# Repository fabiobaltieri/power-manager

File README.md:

USB Power Manager
=================

http://fabiobaltieri.com/2013/03/22/power-manager/

This project is an USB power controller, and allows to control the power lines
of two USB ports and a generic supply line.

Main features:
- Two controllable USB ports (5V)
- One controllable generic supply line, up to 26V
- Overcurrent protection for USB ports
- Voltage and current measurement on both USB and power ports, before and after
  the switch
- Two additional independent relay lines (for switch simulation)
- Programmable delayed switching sequence for all ports

License
-------

This program is free software: you can redistribute it and/or modify
it under the terms of the GNU General Public License as published by
the Free Software Foundation, either version 2 of the License, or
(at your option) any later version.

Contents
--------

    COPYING      text version of the GPL
    README       this file
    bootloader/  source directory for bootloader
    bootloader-util/ source directory for bootloader utility (bootloadHID)
    commandline/ source directory for the "pm" utility
    firmware/    source directory for main firmware
    hardware/    source directory for the hardware design

Firmware and Bootloader
-----------------------

Building requires an avr-gcc toolchain, in the firmware/ or bootloader/
directory, to build run:

    make

Flashing the firmware on the device requires avrdude and a compatible hardware
programmer. Default configuration is stored at the beginning of the Makefile.
To program with the default configuration, run:

    make flash

Fuses can be configured running:

    make fuses

To program the main firmware from the bootloader, use the command:

    make boot

Hardware
--------

All hardware files (schematic, layout and libraries) are in CadSoft Eagle
format.

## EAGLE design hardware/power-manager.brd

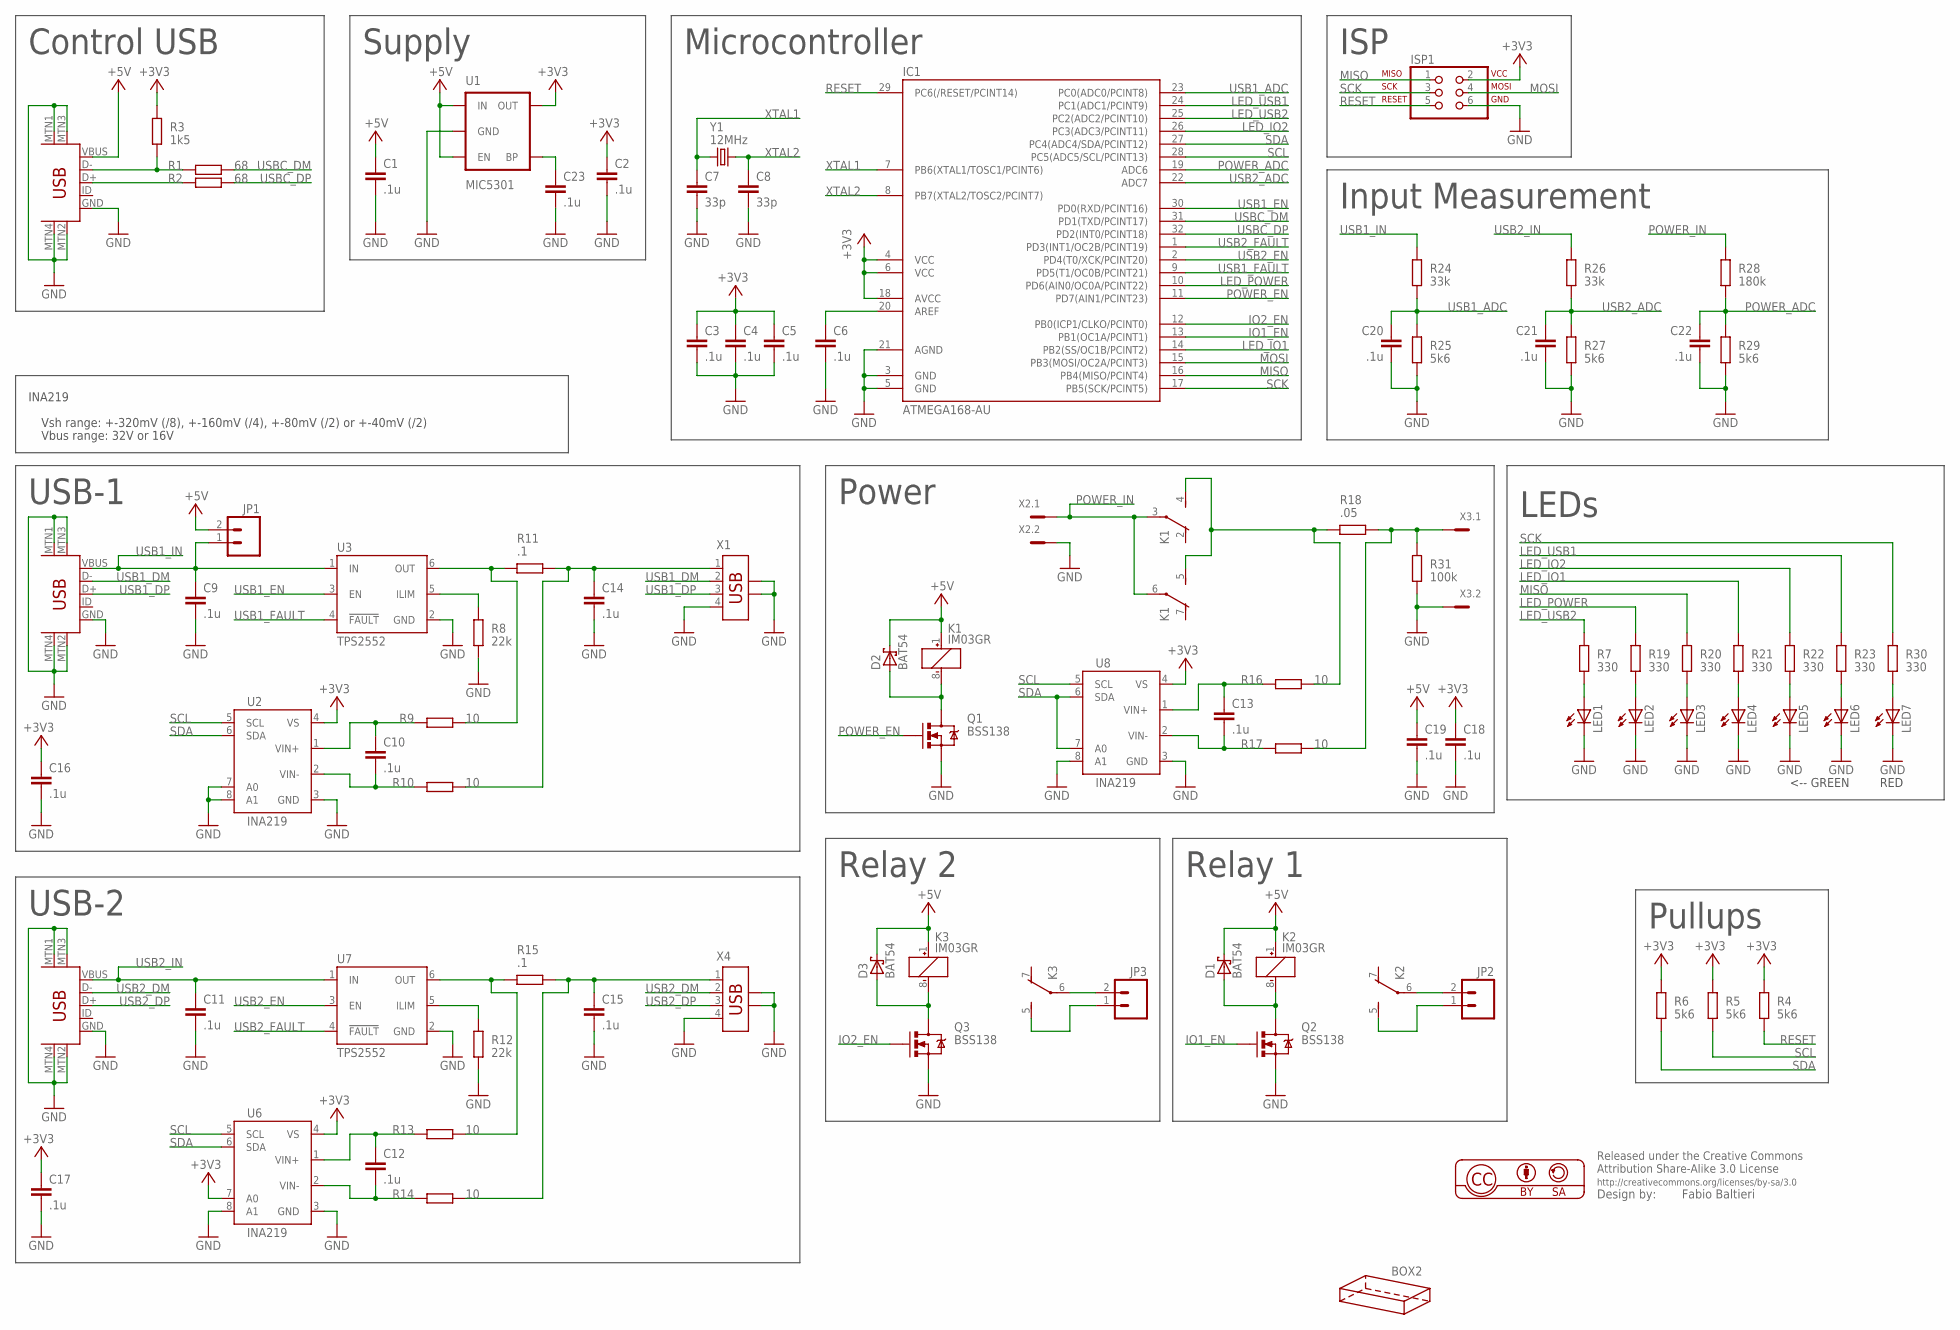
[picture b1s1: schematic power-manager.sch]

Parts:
BOX2: HAMMOND-BOX-K; 1551K
C1, C2, C3, C4, C5, C6, C9, C10, C11, C12, C13, C14, C15, C16, C17, C18, C19, C20, C21, C22, C23: .1u; C0805
C7, C8: 33p; C0805
D1, D2, D3: BAT54; SOT23
IC1: ATMEGA168-AU; TQFP32-08
ISP1: ISP-AVR910PTH; 2X03
JP1, JP2, JP3: M02PTH; 1X02
K1, K2, K3: IM03GR; G6J-2FL-Y
LED1, LED2, LED3, LED4, LED5, LED6, LED7: LEDSML0805; SML0805
Q1, Q2, Q3: BSS138; SOT23-3
R1, R2: 68; R0603
R3: 1k5; R0603
R4, R5, R6, R25, R27, R29: 5k6; R0603
R7, R19, R20, R21, R22, R23, R30: 330; R0603
R8, R12: 22k; R0603
R9, R10, R13, R14, R16, R17: 10; R0603
R11, R15: .1; R0805
R18: .05; R0805
R24, R26: 33k; R0603
R28: 180k; R0603
R31: 100k; R0603
U1: MIC5301; SOT23-5
U2, U6, U8: INA219; SOT23-8L
U3, U7: TPS2552; SOT23-6L
U$1, U$2, U$3: USB-MINIB-5PIN; USB-MINIB
X1, X4: USB-787616; USB
X2, X3: MC2
Y1: 12MHz; CRYSTAL-SMD-5X3

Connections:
+3V3: C2.1, C3.1, C4.1, C5.1, C16.1, C17.1, C18.1, IC1.4 (VCC), IC1.6 (VCC), IC1.18 (AVCC), ISP1.2, R3.1, R4.1, R5.1, R6.1, U1.5 (OUT), U2.4 (VS), U6.4 (VS), U6.7 (A0), U8.4 (VS)
+5V: C1.1, C19.1, D1.3 (C), D2.3 (C), D3.3 (C), JP1.2, K1.1 (+), K2.1 (+), K3.1 (+), U1.1 (IN), U1.3 (EN), U$1.VBUS
GND: C1.2, C2.2, C3.2, C4.2, C5.2, C6.2, C7.2, C8.2, C9.2, C11.2, C14.2, C15.2, C16.2, C17.2, C18.2, C19.2, C20.2, C21.2, C22.2, C23.2, IC1.3 (GND), IC1.5 (GND), IC1.21 (AGND), ISP1.6, LED1.C, LED2.C, LED3.C, LED4.C, LED5.C, LED6.C, LED7.C, Q1.2 (S), Q2.2 (S), Q3.2 (S), R8.2, R12.2, R25.2, R27.2, R29.2, R31.2, U1.2 (GND), U2.3 (GND), U2.7 (A0), U2.8 (A1), U3.2 (GND), U6.3 (GND), U6.8 (A1), U7.2 (GND), U8.3 (GND), U8.8 (A1), U$1.GND, U$1.MTN1 (MTN2), U$1.MTN2 (MTN3), U$1.MTN3 (MTN1), U$1.MTN4, U$2.GND, U$2.MTN1 (MTN2), U$2.MTN2 (MTN3), U$2.MTN3 (MTN1), U$2.MTN4, U$3.GND, U$3.MTN1 (MTN2), U$3.MTN2 (MTN3), U$3.MTN3 (MTN1), U$3.MTN4, X1.4, X1.SHLD1, X1.SHLD2, X2.2, X3.2, X4.4, X4.SHLD1, X4.SHLD2
IO1_EN: IC1.13 (PB1(OC1A/PCINT1)), Q2.1 (G)
IO2_EN: IC1.12 (PB0(ICP1/CLKO/PCINT0)), Q3.1 (G)
LED_IO1: IC1.14 (PB2(SS/OC1B/PCINT2)), R21.1
LED_IO2: IC1.26 (PC3(ADC3/PCINT11)), R22.1
LED_POWER: IC1.10 (PD6(AIN0/OC0A/PCINT22)), R19.1
LED_USB1: IC1.24 (PC1(ADC1/PCINT9)), R23.1
LED_USB2: IC1.25 (PC2(ADC2/PCINT10)), R7.1
MISO: IC1.16 (PB4(MISO/PCINT4)), ISP1.1, R20.1
MOSI: IC1.15 (PB3(MOSI/OC2A/PCINT3)), ISP1.4
unnamed: R1.1, R3.2, U$1.D-
unnamed: C6.1, IC1.20 (AREF)
unnamed: R2.1, U$1.D+
unnamed: R8.1, U3.5 (ILIM)
unnamed: C23.1, U1.4 (BP)
unnamed: C10.2, R10.1, U2.2 (VIN-)
unnamed: C10.1, R9.1, U2.1 (VIN+)
unnamed: R9.2, R11.1, U3.6 (OUT)
unnamed: C14.1, R10.2, R11.2, X1.1
unnamed: LED7.A, R30.2
unnamed: R12.1, U7.5 (ILIM)
unnamed: C12.2, R14.1, U6.2 (VIN-)
unnamed: C12.1, R13.1, U6.1 (VIN+)
unnamed: R13.2, R15.1, U7.6 (OUT)
unnamed: C15.1, R14.2, R15.2, X4.1
unnamed: C13.2, R17.1, U8.2 (VIN-)
unnamed: C13.1, R16.1, U8.1 (VIN+)
unnamed: K1.4 (S), K1.5 (S), R16.2, R18.1
unnamed: R17.2, R18.2, R31.1, X3.1
unnamed: D2.1 (A), K1.8 (-), Q1.3 (D)
unnamed: D1.1 (A), K2.8 (-), Q2.3 (D)
unnamed: JP2.2, K2.6
unnamed: JP2.1, K2.5 (S)
unnamed: D3.1 (A), K3.8 (-), Q3.3 (D)
unnamed: JP3.2, K3.6
unnamed: JP3.1, K3.5 (S)
unnamed: LED1.A, R7.2
unnamed: LED2.A, R19.2
unnamed: LED3.A, R20.2
unnamed: LED4.A, R21.2
unnamed: LED5.A, R22.2
unnamed: LED6.A, R23.2
POWER_ADC: C22.1, IC1.19 (ADC6), R28.2, R29.1
POWER_EN: IC1.11 (PD7(AIN1/PCINT23)), Q1.1 (G)
POWER_IN: K1.3, K1.6, R28.1, X2.1
RESET: IC1.29 (PC6(/RESET/PCINT14)), ISP1.5, R4.2
SCK: IC1.17 (PB5(SCK/PCINT5)), ISP1.3, R30.1
SCL: IC1.28 (PC5(ADC5/SCL/PCINT13)), R5.2, U2.5 (SCL), U6.5 (SCL), U8.5 (SCL)
SDA: IC1.27 (PC4(ADC4/SDA/PCINT12)), R6.2, U2.6 (SDA), U6.6 (SDA), U8.6 (SDA), U8.7 (A0)
USB1_ADC: C20.1, IC1.23 (PC0(ADC0/PCINT8)), R24.2, R25.1
USB1_DM: U$2.D-, X1.2
USB1_DP: U$2.D+, X1.3
USB1_EN: IC1.30 (PD0(RXD/PCINT16)), U3.3 (EN)
USB1_FAULT: IC1.9 (PD5(T1/OC0B/PCINT21)), U3.4 (!FAULT)
USB1_IN: C9.1, JP1.1, R24.1, U3.1 (IN), U$2.VBUS
USB2_ADC: C21.1, IC1.22 (ADC7), R26.2, R27.1
USB2_DM: U$3.D-, X4.2
USB2_DP: U$3.D+, X4.3
USB2_EN: IC1.2 (PD4(T0/XCK/PCINT20)), U7.3 (EN)
USB2_FAULT: IC1.1 (PD3(INT1/OC2B/PCINT19)), U7.4 (!FAULT)
USB2_IN: C11.1, R26.1, U7.1 (IN), U$3.VBUS
USBC_DM: IC1.31 (PD1(TXD/PCINT17)), R1.2
USBC_DP: IC1.32 (PD2(INT0/PCINT18)), R2.2
XTAL1: C7.1, IC1.7 (PB6(XTAL1/TOSC1/PCINT6)), Y1.1
XTAL2: C8.1, IC1.8 (PB7(XTAL2/TOSC2/PCINT7)), Y1.3 (2)

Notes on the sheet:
Microcontroller
Control USB
USB-1
USB-2
Power
Supply
Relay 1
Relay 2
ISP
Pullups
LEDs
INA219
Vsh range: +-320mV (/8), +-160mV (/4), +-80mV (/2) or +-40mV (/2)
Vbus range: 32V or 16V
Input Measurement
RED
<-- GREEN

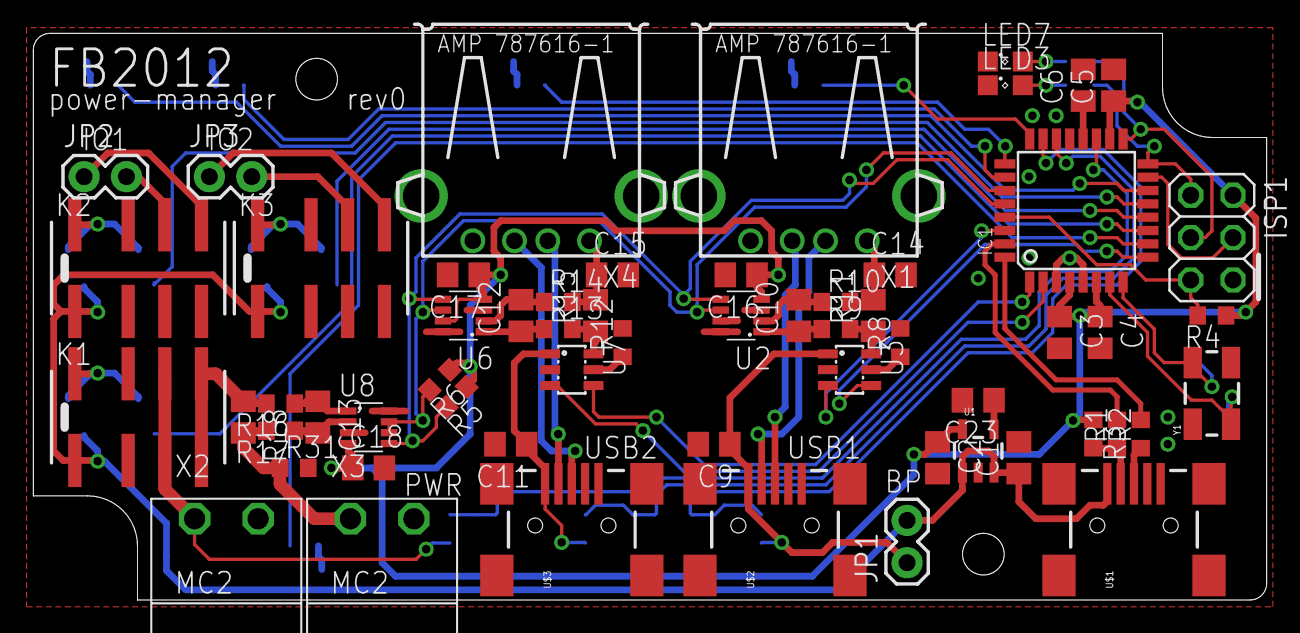
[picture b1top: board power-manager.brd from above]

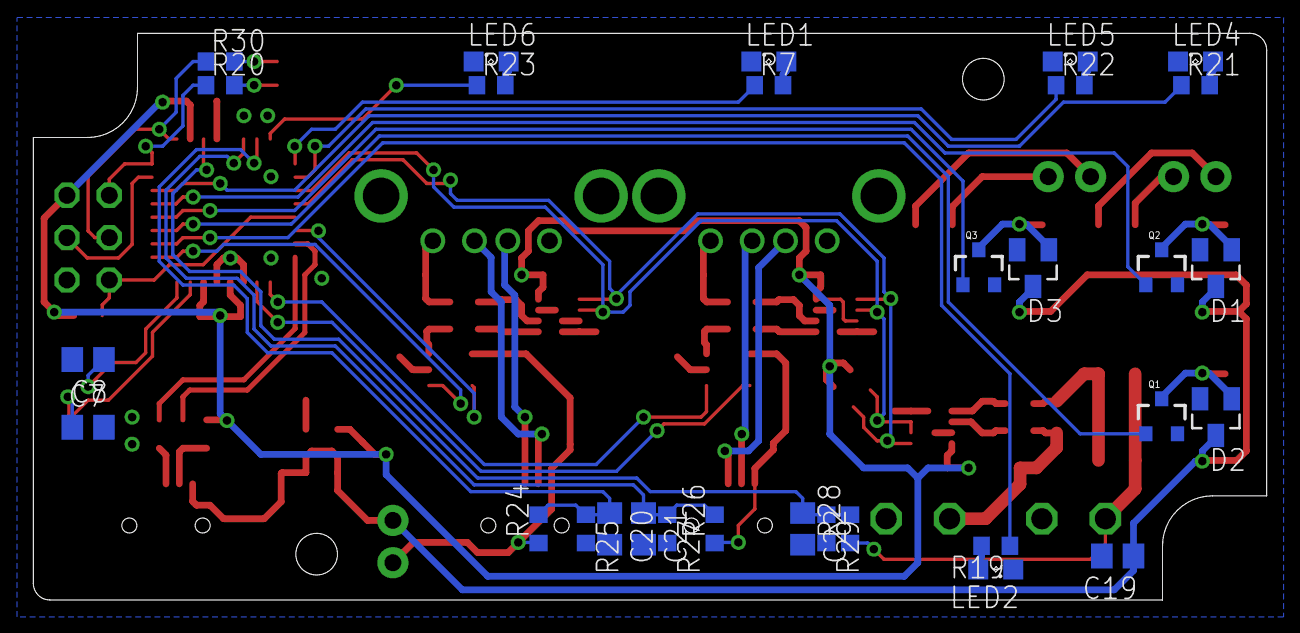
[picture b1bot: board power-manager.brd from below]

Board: 2 copper layers, 74.0 x 34.0 mm, 90 parts (30 on the bottom side), 67 nets.

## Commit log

2012-11-08 hw: rc
2012-11-08 bl: add bootloader from usb-current-meter
2012-11-08 bl: update for gcc 4.7
2012-11-08 bl: fix minor warning
2012-11-10 hw: rc2
2012-11-10 hw: rc3
2012-11-10 hw: rc4?
2012-11-10 hw: rc5
2012-11-10 hw: rc6
2012-11-10 hw: rc7
2012-11-10 hw: rc8
2012-11-25 hw: update hammond library
2012-11-30 bootloader: fix GPIO config
2012-11-30 bl: change clock speed and fuse bytes
2012-11-30 add .gitignore file
2012-11-30 firmware: initial import
2012-11-30 fw: fix led configuration
2012-11-30 fw: allow ld to drop unused text
2012-11-30 fw: add hello... hello!
2012-11-30 fw: move board include
2012-12-12 usbdrv: fix usbconfig.h include to remove -I.
2012-12-12 firmware: new Makefile
2012-12-12 fw: add jiffies
2012-12-12 fw: add stub comments in requests.h
2012-12-12 fw: config for power-manager board
2012-12-12 fw: add io files
2012-12-12 commandline: add commandline stubs
2013-01-14 fw: add version.h
2013-01-14 fw: add events code
2013-01-17 fw: fix wrong boot target
2013-01-17 board: fix led polarity
2013-01-17 hw: update part values
2013-01-17 fw: io: readability fixes
2013-01-17 fw: Makefile: add reset to boot target
2013-01-17 fw: jiffies: use correct timer
2013-01-17 fw: event: s/evt/ev/
2013-01-17 fw: board: remove extra ;
2013-01-17 io: support active low channels
2013-01-17 fw: request implement request definitions
2013-01-17 fw: events: staticize ev_full
2013-01-18 fw: event chain and io working
2013-01-18 fw: io: add adc_get_ch
2013-01-18 fw: io: fix fault reading
2013-01-18 fw: add adc support
2013-01-18 fw: main: fix led startup sequence
2013-01-18 fw: board: add partitor values
2013-01-18 fw: request: update status structure
2013-01-18 fw: main: add adc voltage measurement support function
2013-01-18 fw: adc: remove board include
2013-01-19 fw: add and compile in i2c
2013-01-19 fw: enable i2c and add ina defs
2013-01-19 fw: move div_round upper
2013-01-19 fw: i2c: swap bytes
2013-01-19 fw: change status structure
2013-01-19 fw: i2c: add dynamic frequency selection
2013-01-19 fw: add ina219 configs
2013-01-19 commandline: add status function
2013-01-19 fw: add ina_init code
2013-01-19 fw: fix led holdoff bug
2013-01-20 fw: main: implement update_status
2013-01-20 cmdline: implement all commands
2013-01-20 cmdline: remove debug printf
2013-01-21 fw: add state tracking
2013-01-21 cmdline: print line statuses
2013-01-21 cmdline: big-endian support
2013-02-25 add README and licence files
2013-02-25 add bootloader-util
2013-02-26 hw: add notes and pdf
2013-02-28 README update
2013-03-05 cmdline: add missing newline in help text
2013-03-16 hw: update xtal cap values to 33p
2013-03-18 fw: minor style fix
2013-03-21 hw: update pdf
2013-03-21 README: update directory list
2013-03-22 README: update project website link
2013-03-22 firmware: update license headers on C source files
2013-03-22 cmdline: add license
2013-03-23 fw: usbconfig: use openmoko's assigned ID
    Change main firmware USB vendor and product IDs to the one assigned in
    the Openmoko registry, that can be found at:
    http://wiki.openmoko.org/wiki/USB_Product_IDs
    Assigned IDs: 0x1d50 0x6061 Power Manager
    Thanks Openmoko!
2013-03-23 cmdline: use vendor/product id to find the device path
    As the project has now an assigned vendor:device pair, use that to find
    the right device instead of the product string.
2013-03-24 cmdline: upgrade USB API to libusb-1.0
    And get rid of the custom vid/pid open in favor of
    libusb_open_device_with_vid_pid.
2013-05-21 fw: allow i2c master read to send nack
2013-05-30 binaries: add pre-built binary for atmega168

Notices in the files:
parts and their libraries:
SparkFun-Connectors: Licensing: CC v3.0 Share-Alike You are welcome to use this library for commercial purposes.
balto: Released under the Creative Commons
balto: http://creativecommons.org/licenses/by-sa/3.0
